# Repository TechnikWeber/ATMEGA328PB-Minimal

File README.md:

# ATmega328PB minimal board

<p>

</p>

A minimal breakout board for the ATmega328PB (TQFP-32): just what the chip needs to run,
be programmed and talk to a PC — a starting point for small AVR projects.

## What is on it

| Part | Purpose |
|---|---|
| ATmega328PB-A (TQFP-32) | The microcontroller, on its internal oscillator |
| 2×3 ISP header | Programming with any AVR ISP programmer (USBasp, AVRISP mkII, …) |
| 1×6 header for an FTDI TTL-232R-3V3 cable | Serial connection and 3.3 V power from a USB-UART cable; DTR/RTS allows auto-reset for a bootloader |
| RESET and USER buttons | Reset, and one button for your own firmware |
| LED with 220 Ω | Status LED |
| 3 × 100 nF, 10 kΩ reset pull-up | Decoupling and reset |

## Files

- `ATMEGA328PB_Minimal.kicad_sch` / `.kicad_pcb` — schematic and PCB (KiCad)

## License

[MIT](LICENSE).

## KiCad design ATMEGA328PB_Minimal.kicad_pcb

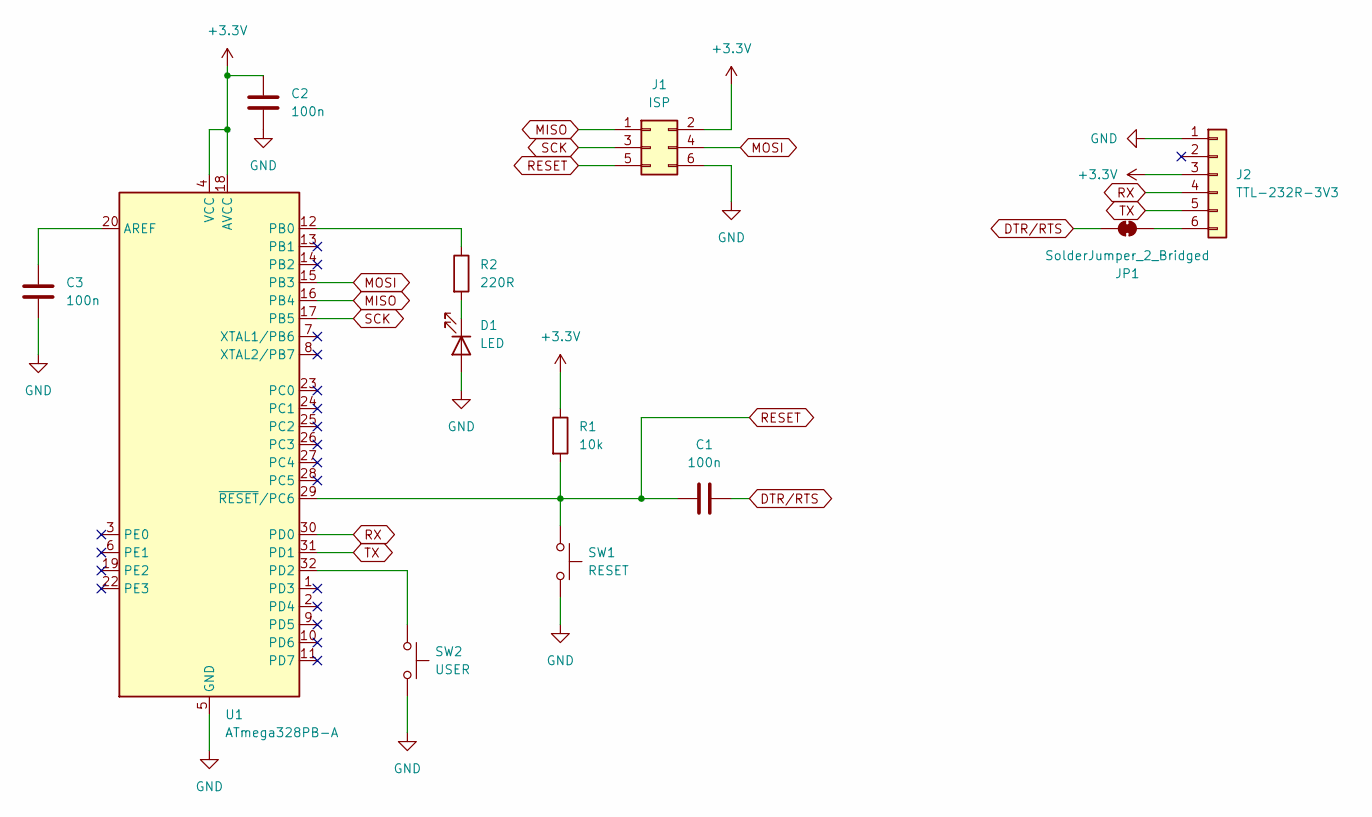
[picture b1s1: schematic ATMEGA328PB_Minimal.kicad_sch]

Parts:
C1, C2, C3: 100n; C_0805_2012Metric
D1: LED; C_0805_2012Metric
J1: ISP; PinHeader_2x03_P2.54mm_Vertical
J2: TTL-232R-3V3; PinHeader_1x06_P2.54mm_Vertical
JP1: SolderJumper_2_Bridged; SolderJumper-2_P1.3mm_Bridged_Pad1.0x1.5mm
R1: 10k; R_0805_2012Metric
R2: 220R; R_0805_2012Metric
SW1: RESET; SW_PUSH_6mm_H4.3mm
SW2: USER; SW_PUSH_6mm_H4.3mm
U1: ATmega328PB-A; TQFP-32_7x7mm_P0.8mm

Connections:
+3.3V: C2.1, J1.2, J2.3, R1.1, U1.4 (VCC), U1.18 (AVCC)
DTR/RTS: C1.2, JP1.2 (B)
GND: C2.2, C3.1, D1.2 (A), J1.6, J2.1, SW1.2, SW2.2, U1.5 (GND), U1.21 (GND)
MISO: J1.1, U1.16 (PB4)
MOSI: J1.4, U1.15 (PB3)
unnamed: D1.1 (K), R2.2
unnamed: J2.6, JP1.1 (A)
unnamed: C3.2, U1.20 (AREF)
unnamed: R2.1, U1.12 (PB0)
unnamed: SW2.1, U1.32 (PD2)
RESET: C1.1, J1.5, R1.2, SW1.1, U1.29 (~RESET/PC6)
RX: J2.4, U1.30 (PD0)
SCK: J1.3, U1.17 (PB5)
TX: J2.5, U1.31 (PD1)

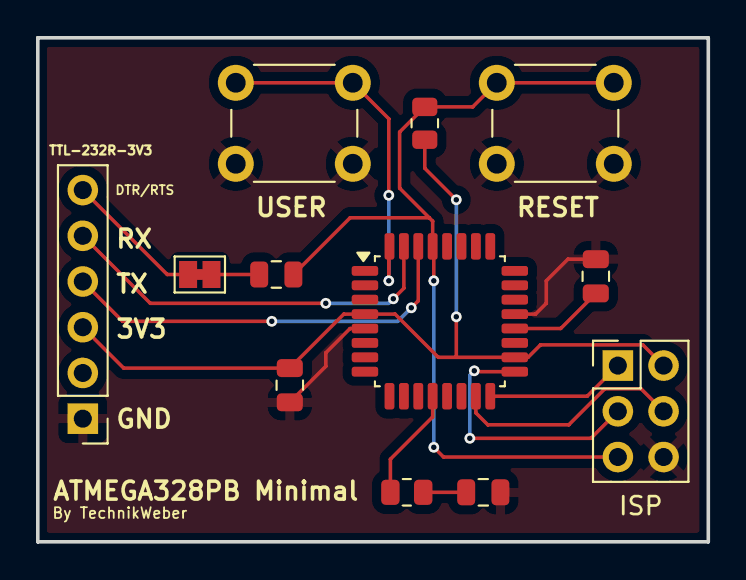
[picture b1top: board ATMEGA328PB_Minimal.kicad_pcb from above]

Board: 2 copper layers, 37.2 x 28.0 mm, 12 parts (0 on the bottom side), 14 nets.

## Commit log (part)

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2026-03-20 Add image to README file
